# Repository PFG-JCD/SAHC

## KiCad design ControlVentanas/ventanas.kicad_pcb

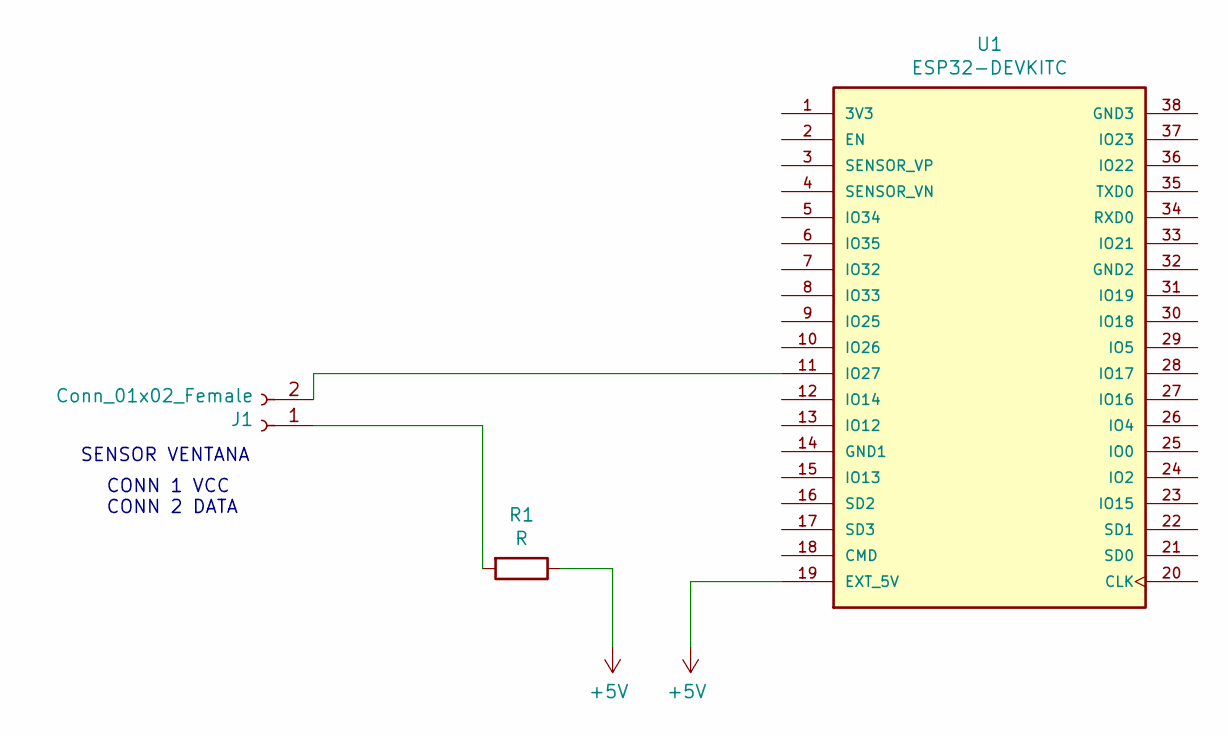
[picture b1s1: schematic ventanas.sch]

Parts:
J1: Conn_01x02_Female; Banana_Jack_2Pin
R1: R; R_0815_2038Metric_Pad1.20x4.05mm_HandSolder
U1: ESP32-DEVKITC; MODULE_ESP32-DEVKITC; PARTREV N/A

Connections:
+5V: R1.1, U1.19 (EXT_5V)
unnamed: J1.1, R1.2
unnamed: J1.2, U1.11 (IO27)

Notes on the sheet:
SENSOR VENTANA
CONN 1 VCC CONN 2 DATA

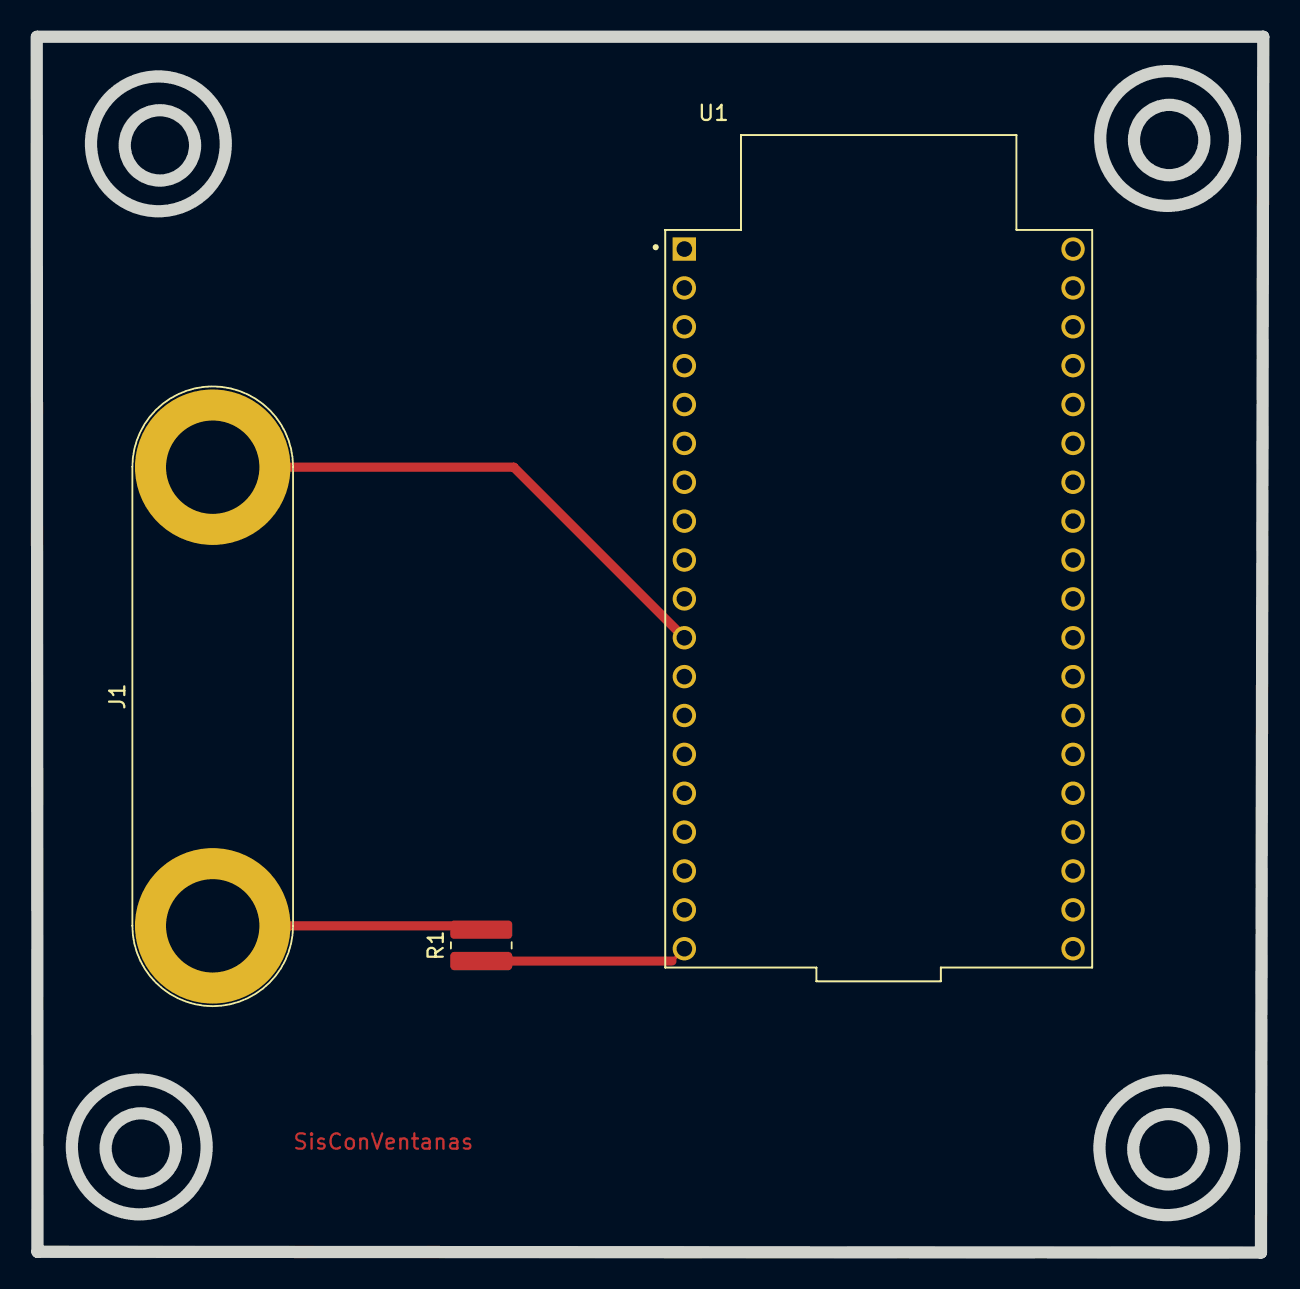
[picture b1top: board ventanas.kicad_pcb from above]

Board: 2 copper layers, 80.2 x 79.5 mm, 3 parts (0 on the bottom side), 3 nets.

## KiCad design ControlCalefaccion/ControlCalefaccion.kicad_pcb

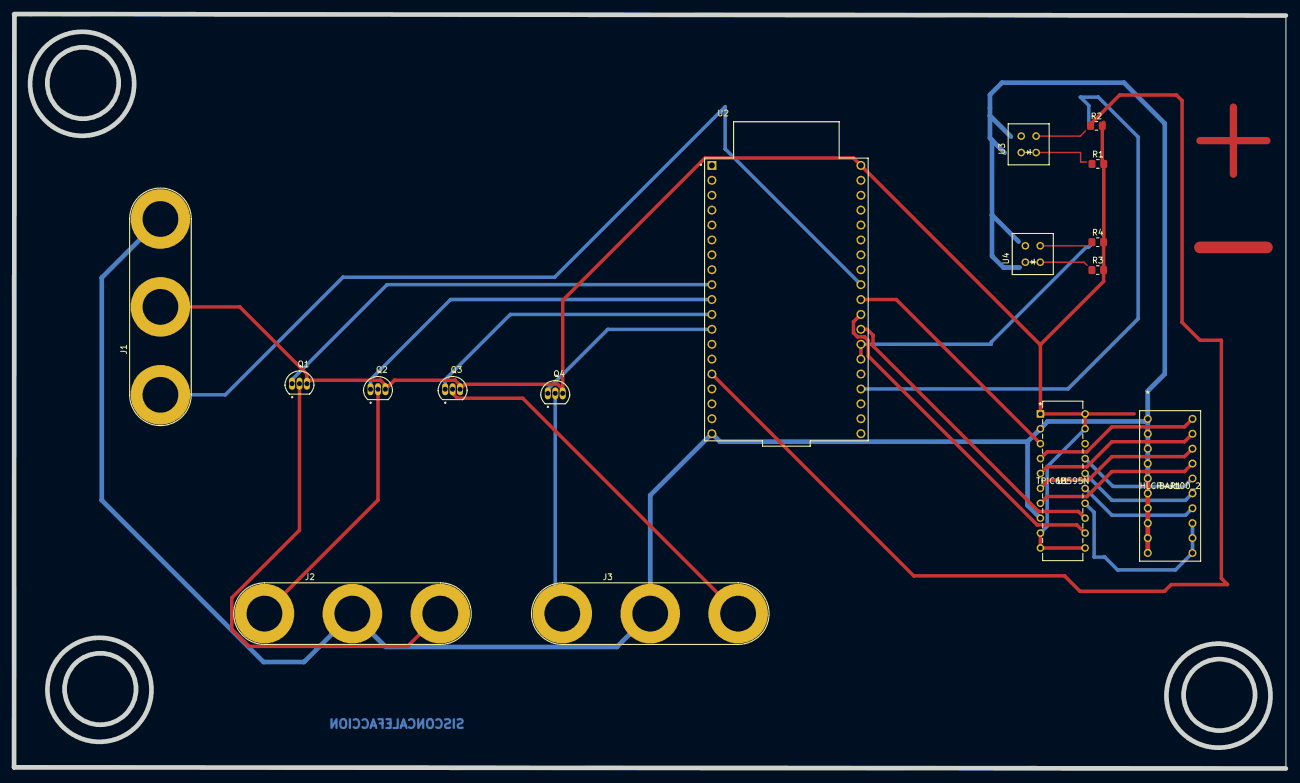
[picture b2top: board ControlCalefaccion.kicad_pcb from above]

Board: 2 copper layers, 216.8 x 128.6 mm, 16 parts (0 on the bottom side), 24 nets.

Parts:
BAR1: HLCP-J100_2; HLCP-J100
J1, J2, J3: Conn_01x03_Female; Banana_Jack_3Pin
Q1, Q2, Q3, Q4: Q_NPN_BCE; TO92127P495H495-3
R1, R2, R3, R4: R; R_0805_2012Metric_Pad1.20x1.40mm_HandSolder
U1: TPIC6B595N
U2: ESP32-DEVKITC; MODULE_ESP32-DEVKITC
U3, U4: CNY70; DIPS254W50P254L710H600Q4

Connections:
+5V: BAR1.1, BAR1.2, BAR1.3, BAR1.4, BAR1.5, BAR1.6, BAR1.7, BAR1.8, BAR1.9, BAR1.10, J1.3, J2.2, J3.2, U1.2, U1.8, U2.19
GND: J1.2, Q1.3, Q2.3, Q3.3, Q4.3, R1.2, R2.2, R3.2, R4.2, U1.1, U1.9, U1.10, U1.11, U1.19, U1.20, U2.38
unnamed: BAR1.11, BAR1.12, BAR1.13, U1.14
unnamed: BAR1.14, U1.15
unnamed: BAR1.15, U1.16
unnamed: BAR1.16, U1.17
unnamed: BAR1.17, U1.7
unnamed: BAR1.18, U1.6
unnamed: BAR1.19, U1.5
unnamed: BAR1.20, U1.4
unnamed: J1.1, U2.30
unnamed: J2.1, Q2.2
unnamed: J2.3, Q1.2
unnamed: J3.1, Q4.2
unnamed: J3.3, Q3.2
unnamed: Q1.1, U2.9
unnamed: Q2.1, U2.10
unnamed: Q3.1, U2.11
unnamed: Q4.1, U2.12
unnamed: R2.1, U2.15
unnamed: R4.1, U2.25, U2.26
unnamed: U1.3, U2.29
unnamed: U1.12, U2.28
unnamed: U1.13, U2.27

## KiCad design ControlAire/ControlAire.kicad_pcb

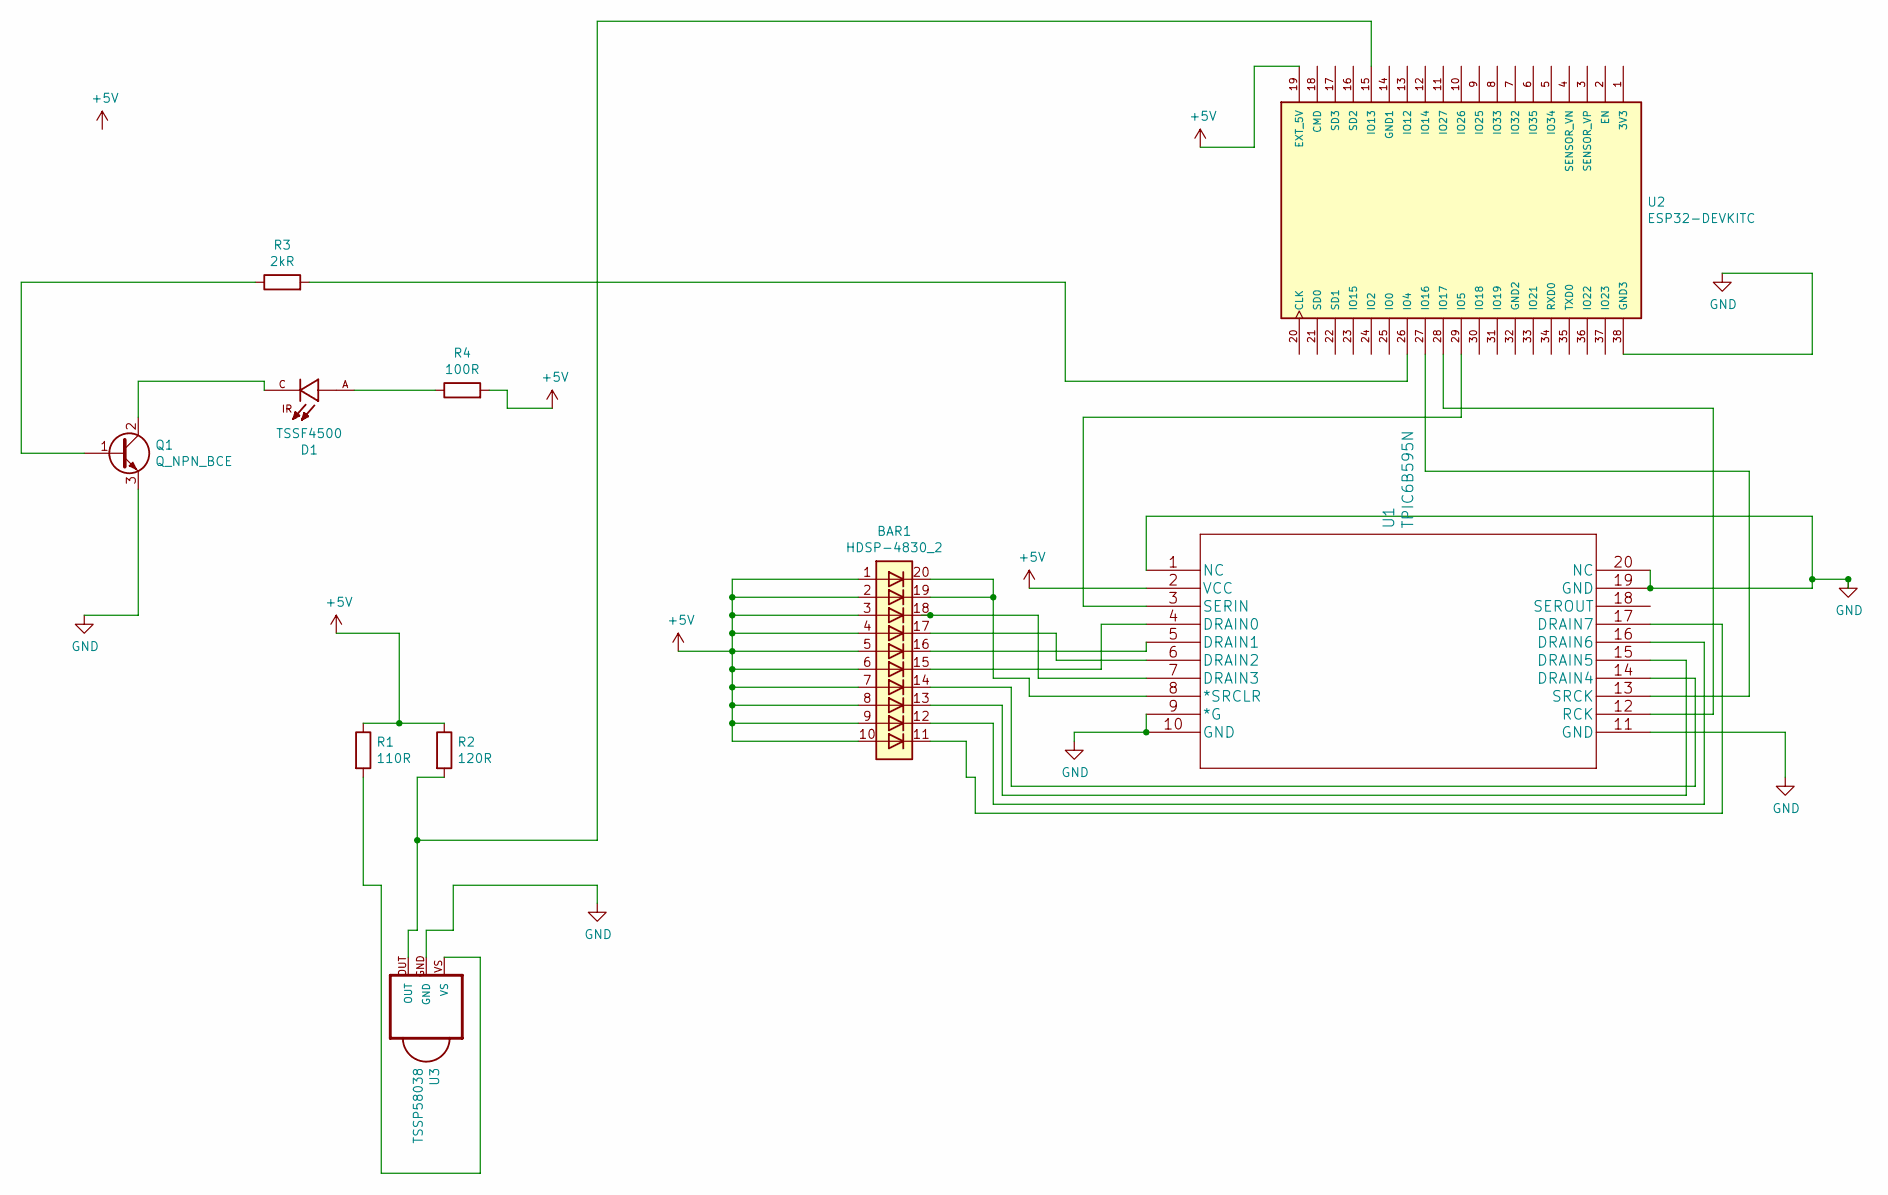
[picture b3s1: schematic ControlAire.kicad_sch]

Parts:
BAR1: HDSP-4830_2; HLCP-J100
D1: TSSF4500; DIO_TSSF4500; PARTREV 1.7
Q1: Q_NPN_BCE; TO92250P510H770-3
R1: 110R; R_Axial_DIN0204_L3.6mm_D1.6mm_P5.08mm_Horizontal
R2: 120R; R_Axial_DIN0204_L3.6mm_D1.6mm_P5.08mm_Horizontal
R3: 2kR; R_Axial_DIN0204_L3.6mm_D1.6mm_P5.08mm_Horizontal
R4: 100R; R_Axial_DIN0204_L3.6mm_D1.6mm_P5.08mm_Horizontal
U1: TPIC6B595N; DIP254P762X508-20
U2: ESP32-DEVKITC; MODULE_ESP32-DEVKITC-32D; PARTREV N/A
U3: TSSP58038

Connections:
+5V: BAR1.1 (A), BAR1.2 (A), BAR1.3 (A), BAR1.4 (A), BAR1.5 (A), BAR1.6 (A), BAR1.7 (A), BAR1.8 (A), BAR1.9 (A), BAR1.10 (A), R1.1, R2.1, R4.2, U1.2 (VCC), U2.19 (EXT_5V)
GND: Q1.3 (E), U1.1 (NC), U1.9 (*G), U1.10 (GND), U1.11 (GND), U1.19 (GND), U1.20 (NC), U2.38 (GND3), U3.GND
unnamed: BAR1.11 (K), U1.17 (DRAIN7)
unnamed: BAR1.12 (K), U1.16 (DRAIN6)
unnamed: BAR1.13 (K), U1.15 (DRAIN5)
unnamed: BAR1.14 (K), U1.14 (DRAIN4)
unnamed: BAR1.15 (K), U1.4 (DRAIN0)
unnamed: BAR1.16 (K), U1.5 (DRAIN1)
unnamed: BAR1.17 (K), U1.6 (DRAIN2)
unnamed: BAR1.18 (K), U1.7 (DRAIN3)
unnamed: BAR1.19 (K), BAR1.20 (K), U1.8 (*SRCLR)
unnamed: D1.A, R4.1
unnamed: D1.C, Q1.2 (C)
unnamed: Q1.1 (B), R3.1
unnamed: R1.2, U3.VS
unnamed: R2.2, U2.15 (IO13), U3.OUT
unnamed: R3.2, U2.26 (IO4)
unnamed: U1.3 (SERIN), U2.29 (IO5)
unnamed: U1.12 (RCK), U2.28 (IO17)
unnamed: U1.13 (SRCK), U2.27 (IO16)

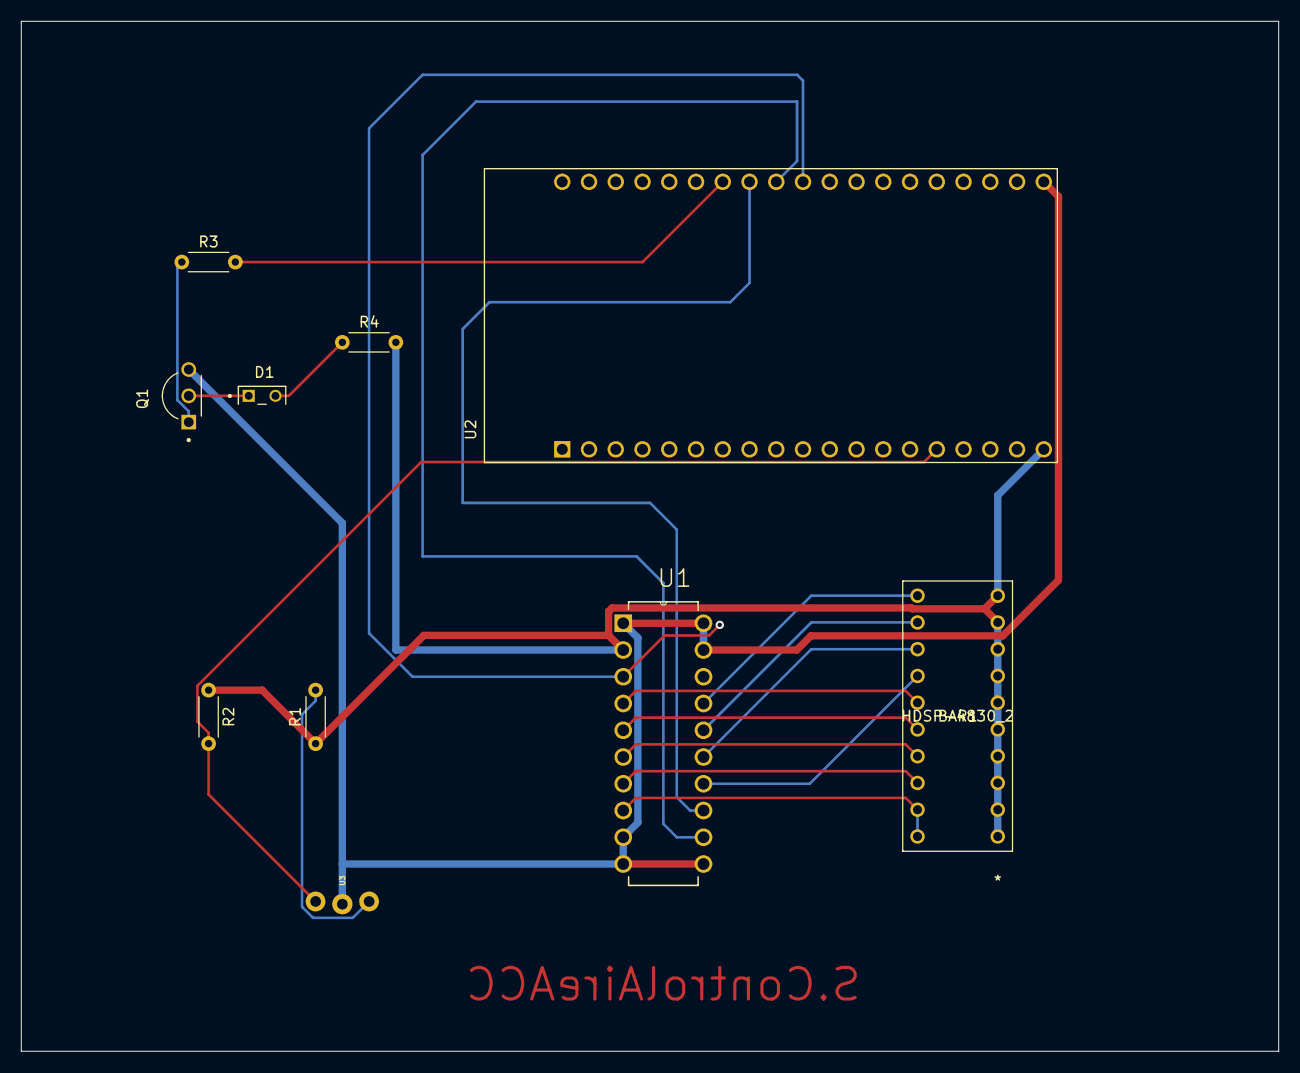
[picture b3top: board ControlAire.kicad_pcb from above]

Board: 2 copper layers, 119.4 x 97.8 mm, 10 parts (0 on the bottom side), 20 nets.

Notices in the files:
parts and their libraries:
Copyright 2021 Accelerated Designs. All rights reserved.
